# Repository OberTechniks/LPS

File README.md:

# LPS
DIY Lab Power Supply with adjustable voltage and current limiting

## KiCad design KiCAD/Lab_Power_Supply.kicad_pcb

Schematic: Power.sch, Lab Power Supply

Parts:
BAT1, BAT2: 2600mAH; Keystone_Electronics_54; Charge Voltage 4.2V Charge; Manufacturer Part# 54
C1, C9, C12, C13, C15, C16: 0.1uF; C_0805; Manufacturer Part# C0805C104K5RACTU
C2, C3, C4, C17: 47nF; C_0805; Manufacturer Part# C0805C473K5RACTU
C5, C10: 2.2uF; C_0805; Manufacturer Part# UMK212BB7225KG-T
C6: 1nF; C_0805; Manufacturer Part# C0805C102K5RACTU
C7, C8: 0.22uF; C_0805; Manufacturer Part# UMK212B7224KG-T
C11: 1.0uF; C_0805; Manufacturer Part# CL21B105KOFNNNG
C14: 22uF; C_0805; Manufacturer Part# JMK212BJ226MG-T
C18, C19: 100uF; CP_Radial_D8.0mm_P3.50mm; Manufacturer Part# ESY107M050AG3AA
D1: 22V; D_SMA; Manufacturer Part# SMAZ22-13-F
D2: SCR; TO-252-3_TabPin2; Manufacturer Part# MCR12DCMT4G
D3: D_Schottky_ALT; D_SMC; Manufacturer Part# MBRS340T3G
D6: D_Schottky_ALT; D_SMC; Manufacturer Part# MBRS360T3G
F1: 3A; R_1206_HandSoldering; Manufacturer Part# C1Q 3
F2: 6A; R_1206_HandSoldering; Manufacturer Part# C1F 6
J1: BARREL_JACK; PJ-066A; Manufacturer Part# PJ-066A
L1: 10uH; IFSC1515AHER100M01; Manufacturer Part# IFSC1515AHER100M01
L2: 33uH; SRP1265A-330M; Manufacturer Part# SRP1265A-330M
L3: 1uH; 2520_Metric; Manufacturer Part# CIG22E1R0MNE
L4: Ferrite; C_0805; Manufacturer Part# BMB2A0300LN2
Q1: MOSFET N-CH 20V 0.2A EMT3; SC-89; Manufacturer Part# RE1C002UNTCL
Q2: Q_PMOS_GDS; TO-252-3_TabPin2; Manufacturer Part# AOD4189
R1: 1K; R_2512; Manufacturer Part# CRM2512-JW-102ELF
R2: 120; R_0805; Manufacturer Part# RC0805FR-07120RL
R3, R4, R5, R6, R7, R9, R10, R11: 100K; R_0805; Manufacturer Part# RC0805FR-07100KL
R8: 10K; R_0805; Manufacturer Part# RMCF0805JT10K0
R12, R13: 4.7; R_0805; Manufacturer Part# CRCW08054R70FKEA
R14: 0.04; R_2512; Manufacturer Part# CRA2512-FZ-R040ELF
R15: 6.8; R_2512; Manufacturer Part# RPC2512JT6R80
R16: 0.03; R_2512; Manufacturer Part# CRA2512-FZ-R030ELF
TP2, TP3, TP4, TP5, TP6, TP7, TP8, TP9, TP10: TestPoint; SMT_Test_Point; Manufacturer Part# S1751-46R
U4: MAX1873; QSOP-16_3.9x4.9mm_Pitch0.635mm; Manufacturer Part# MAX1873REEE+T
U5: TPS62177; 10-WSON; Manufacturer Part# TPS62177DQCR

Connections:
+3V3: C17.1, L4.2, TP4.1; also elsewhere on the board
/Control/CHARGE_~EN~: R2.2; also elsewhere on the board
/Control/CHG_SENSE_+: L2.2, R16.2, U4.11; also elsewhere on the board
/Control/CHG_SENSE_-: C19.1, F2.1, R16.1, TP3.1, U4.10; also elsewhere on the board
/Control/ICHG_ANALOG: TP10.1, U4.7; also elsewhere on the board
/Output/VSYS: C5.1, C18.1, Q2.3, R13.2, R14.1, TP2.1, U5.2, U5.3; also elsewhere on the board
/Power/VREF: C11.1, R4.1, R10.1, TP9.1, U4.9
/Power/~SLEEP~: U5.8
GND: BAT2.2, C1.2, C2.2, C3.2, C4.2, C5.2, C6.2, C7.1, C9.2, C10.2, C11.2, C12.2, C13.2, C14.2, C15.2, C16.2, C17.2, C18.2, C19.2, D2.1 (K), D6.2, J1.2, J1.3, Q1.2, R1.2, R3.2, R7.2, R11.2, TP5.1, TP6.1, TP7.1, TP8.1, U4.12, U5.1, U5.4, U5.5, U5.6, U5.PAD; also elsewhere on the board
unnamed: BAT1.1, F2.2
unnamed: BAT1.2, BAT2.1
unnamed: C1.1, D1.1, D2.2 (A), D3.2, F1.2
unnamed: C2.1, D1.2, D2.3 (G), R1.1
unnamed: C3.1, U4.5
unnamed: C4.1, U4.3
unnamed: C6.1, R8.1, U4.4
unnamed: C7.2, C8.2, D3.1, R12.2, R14.2, U4.15
unnamed: C8.1, U4.13
unnamed: C9.1, R8.2
unnamed: C10.1, U4.16
unnamed: C12.1, R12.1, U4.2
unnamed: C13.1, R13.1, U4.1
unnamed: C14.1, C15.1, L1.2, L3.1, R9.1, R15.1, U5.10
unnamed: C16.1, L3.2, L4.1, R15.2
unnamed: D6.1, L2.1, Q2.2
unnamed: F1.1, J1.1
unnamed: L1.1, U5.9
unnamed: Q1.1, R2.1, R3.1
unnamed: Q1.3, R6.2, R7.1, U4.6
unnamed: Q2.1, U4.14
unnamed: R4.2, R5.1
unnamed: R5.2, R6.1
unnamed: R9.2, U5.7
unnamed: R10.2, R11.1, U4.8

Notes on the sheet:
Ichg = 0.2V(Vichg / Vref)/Rcsb Vichg / Vref = 1/4 Rcsb = 0.030 Ohms Ichg = 1.67A
Vichg = (1/4) Vref = 1.05V Drop below 500mV to disable charging
Input Current Limit Iin = 0.1V/RCSS 0.1V/0.04 = 2.5A
DC INPUT, 12V-20V, 2.5A
BATTERY CHARGING & SYSTEM VOLTAGE
DIGITAL POWER RAIL
Max Output 3.3V, 500mA
TEST POINTS

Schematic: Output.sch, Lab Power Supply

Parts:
C20: 6800pF; C_0805; Manufacturer Part# C0805C682K5RACTU
C21, C34: 47pF; C_0805; Manufacturer Part# 500R15N470JV4T
C22: 4.7uF; C_0805; Manufacturer Part# CL21A475KLCLQNC
C23, C24, C25, C27, C35: 22uF; CP_Elec_6.3x5.3; Manufacturer Part# EEE-1HA220WP
C26, C28, C29, C30, C31, C62: 0.1uF; C_0805; Manufacturer Part# C0805C104K5RACTU
C32: 1nF; C_0805; Manufacturer Part# C0805C102K5RACTU
C33: 22pF; C_0805; Manufacturer Part# C0805C220J5GACTU
D7: D_Schottky_AAK; V20PW10-M3; Manufacturer Part# V20PW10-M3/I
D8, D9, D11: D_Schottky_ALT; D_SMC; Manufacturer Part# MBRS360T3G
D10: 10V; D_MiniMELF; Manufacturer Part# TZM5240B-GS08
D12: 24V; D_SMA; Manufacturer Part# 3SMAJ5934B-TP
F3: 2A; R_1206; Manufacturer Part# C1Q 2
J2: OUTPUT; SolderWirePad_2x_2mmDrill; Manufacturer Part# 43650-0228
L5: 1uH; SRP1245A-1R0M; Manufacturer Part# SRP1245A-1R0M
Q3: Q_NMOS_GDS; TO-252-2; Manufacturer Part# IRLR6225TRPBF
Q4: Q_PNP_BEC; SOT-23; Manufacturer Part# MMBT4403
Q5: Q_PMOS_GDS; TO-220-3_Vertical; Manufacturer Part# IRF9640PBF
Q6: Q_NMOS_GDS; TO-263-2; Manufacturer Part# IRF530NSTRLPBF
R17, R18, R19, R29, R31, R32, R38: 10K; R_0805; Manufacturer Part# RMCF0805JT10K0
R20: 80.6K; R_0805; Manufacturer Part# RC0805FR-0780K6L
R21, R36: 4.7K; R_0805; Manufacturer Part# RC0805JR-074K7L
R22, R23: 100K; R_0805; Manufacturer Part# RC0805FR-07100KL
R24, R25: 1M; R_0805; Manufacturer Part# RC0805JR-071ML
R26: 1K; R_0805; Manufacturer Part# CRM2512-JW-102ELF
R27: 3K; R_0805; Manufacturer Part# RC0805FR-073KL
R28: 27K; R_0805; Manufacturer Part# RC0805FR-0727KL
R30, R37, R40: 1K; R_2512; Manufacturer Part# CRM2512-JW-102ELF
R33: 47K; R_0805; Manufacturer Part# RC0805JR-0747KL
R34: 120; R_0805; Manufacturer Part# RC0805FR-07120RL
R35: 470; R_0805; Manufacturer Part# RC0805JR-07470RL
R39: .1; R_1206; Manufacturer Part# PT1206FR-070R1L
SW5: SW_SPST; R1966ABLKBLKGR; Manufacturer Part# R1966ABLKBLKGR
TP11, TP12, TP13, TP14, TP15, TP16, TP17: TestPoint; SMT_Test_Point; Manufacturer Part# S1751-46R
U2, U3: LM324; SOIC-14_3.9x8.7mm_Pitch1.27mm; Manufacturer Part# LM324ADR
U6: LTC1871-1; MSOP-10_3x3mm_Pitch0.5mm; Manufacturer Part# LTC1871EMS-1#PBF
U7: MCP40D17T-104E/LT; SOT-363_SC-70-6; Manufacturer Part# MCP40D17T-104E/LT

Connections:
+3V3: C24.1, C25.1, C26.1, C27.1, C28.1, C29.1, D7.3, D10.1, Q5.3, R37.2, TP11.1, U2.4 (V+), U3.4 (V+), U7.1 (VDD), U7.6 (W); also elsewhere on the board
/Control/BOOST_EN: R17.2, TP16.1, U6.1; also elsewhere on the board
/Control/CURRENT_SET: R30.2; also elsewhere on the board
/Control/I2C_SCL: U7.4 (SDA); also elsewhere on the board
/Control/I2C_SDA: U7.3 (SCL); also elsewhere on the board
/Control/ISENSE_+: D11.1, R22.1, R38.2, R39.2; also elsewhere on the board
/Control/ISENSE_-: C35.1, D12.1, F3.2, Q6.2, R23.1, R32.1, R39.1; also elsewhere on the board
/Control/VOLTAGE_SET: U2.3 (+); also elsewhere on the board
/Output/GATE: Q3.1, TP13.1, U6.7
/Output/INTVCC: C22.1, TP14.1, U6.5, U6.8
/Output/ITH: C21.2, R18.2, TP15.1, U6.2
/Output/OUTPUT: J2.1, SW5.2, TP12.1
/Output/VSYS: C23.1, C62.1, L5.1, U6.9; also elsewhere on the board
GND: C20.1, C21.1, C22.2, C23.2, C24.2, C25.2, C26.2, C27.2, C28.2, C29.2, C30.2, C35.2, C62.2, D8.1, J2.2, Q3.3, Q4.3, Q6.3, R17.1, R20.1, R21.1, R24.2, R26.2, R27.2, R29.1, R38.1, R40.1, TP17.1, U2.11 (V-), U3.11 (V-), U6.6, U7.2 (VSS); also elsewhere on the board
unnamed: C20.2, R19.1
unnamed: C30.1, R28.2, R29.2, R31.2, U2.1
unnamed: C31.1, C32.2, R35.2, U3.7
unnamed: C31.2, R30.1, U3.6 (-)
unnamed: C32.1, D9.2, R35.1
unnamed: C33.1, C34.1, R36.2, U2.7
unnamed: C33.2, R33.2
unnamed: C34.2, R34.2
unnamed: D7.1, D7.2, L5.2, Q3.2, U6.10
unnamed: D8.2, R32.2, U2.5 (+)
unnamed: D9.1, D10.2, Q4.1, R36.1
unnamed: D11.2, Q5.2
unnamed: D12.2, Q6.1, R40.2
unnamed: F3.1, SW5.1
unnamed: Q4.2, Q5.1, R37.1
unnamed: R18.1, R19.2
unnamed: R20.2, U6.4
unnamed: R21.2, U6.3, U7.5 (B)
unnamed: R22.2, R24.1, U3.3 (+)
unnamed: R23.2, R25.1, U3.2 (-)
unnamed: R25.2, R26.1, U3.1, U3.5 (+)
unnamed: R27.1, R28.1, U2.2 (-)
unnamed: R31.1, R33.1, R34.1, U2.6 (-)

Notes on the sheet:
BOOST CONVERTER PRE-REGULATION
TEST POINTS
CONSTANT VOLTAGE LOOP
CONSTANT CURRENT LOOP
VCC = 1.230V*(1+R1/R2)
100K DIGITAL POT

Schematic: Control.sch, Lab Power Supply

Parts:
C36, C37, C38, C39, C40, C41, C42, C43, C44, C45, C46, C47, C49, C50, C51, C54, C55, C57, C58, C61: 0.1uF; C_0805; Manufacturer Part# C0805C104K5RACTU
C48: 22uF; R_0805; Manufacturer Part# JMK212BJ226MG-T
C52, C53: 12pF; C_0805; Manufacturer Part# CL21C120JBANNNC
C56, C59: 22uF; C_0805; Manufacturer Part# JMK212BJ226MG-T
C60: 1.0uF; C_0805; Manufacturer Part# CL21B105KOFNNNG
D13: 568-0102-173F; Manufacturer Part# 5680102173F
D14: B; APG0603PBC-TT-5MAV; Manufacturer Part# APG0603PBC-TT-5MAV
J3: ICSP_Header; Socket_Strip_Straight_1x06_Pitch2.54mm
J4: Debug Connector; Socket_Strip_Straight_1x06_Pitch2.54mm; Manufacturer Part# M20-9990646
JP1, JP2, JP3, JP4: Jumper_3_Pos; Socket_Strip_Straight_1x03_Pitch2.54mm; Manufacturer Part# 61300311121
Q7, Q8, Q9, Q10, Q11: MOSFET N-CH 20V 0.2A EMT3; SC-89; Manufacturer Part# RE1C002UNTCL
Q12: Q_PMOS_GSD; SOT-23; Manufacturer Part# FDN302P
Q13: Q_PNP_BEC; MMBT3906TT1G; Manufacturer Part# MMBT3906TT1G
R41, R43, R45, R46, R48, R49, R55, R56, R86, R90, R98: 120; R_0805; Manufacturer Part# RC0805FR-07120RL
R42, R44, R47, R50, R59, R60, R61, R88: 100K; R_0805; Manufacturer Part# RC0805FR-07100KL
R51, R52, R53, R54, R57, R58, R62, R63, R64, R65, R66, R67, R68, R69, R70, R74, R78, R79, R80, R81, R87, R89, R97: 10K; R_0805; Manufacturer Part# RMCF0805JT10K0
R71, R72, R76, R77: 10; R_0805; Manufacturer Part# RC0805JR-0710RL
R73, R82, R83, R99: 0; R_0805; Manufacturer Part# RMCF0805ZT0R00
R75: 470; R_0805; Manufacturer Part# RC0805JR-07470RL
R84, R85, R91, R92, R93, R94, R95, R96: 4.7K; R_0805; Manufacturer Part# RC0805JR-074K7L
RV1: 10K; 3361P-1-103GLF; Manufacturer Part# 3361P-1-103GLF
SW1, SW2: EN11-VSM1AF20; Manufacturer Part# EN11-VSM1AF20
SW3: SW_Push; TL1105SF160Q; Manufacturer Part# TL1105SF160Q
SW6: Reset; 7914J-1-000E; Manufacturer Part# 7914J-1-000E
TP18, TP19, TP20, TP21, TP22, TP23, TP24, TP25, TP26, TP27: TestPoint; SMT_Test_Point; Manufacturer Part# S1751-46R
U1: 74HC14; TSSOP-14_4.4x5mm_Pitch0.65mm; Manufacturer Part# SN74HC14PWR
U8: INA226AIDGSR; MSOP-10_3x3mm_Pitch0.5mm; Manufacturer Part# INA226AIDGSR
U9: PIC32MX350F256L-I/PT; TQFP-100_12x12mm_Pitch0.4mm; Manufacturer Part# PIC32MX350F256L-I/PT
U10: 23LC512; SOIC-8_3.9x4.9mm_Pitch1.27mm; Manufacturer Part# 23LC512-I/SN
U11: MCP4822; SOIC-8_3.9x4.9mm_Pitch1.27mm; Manufacturer Part# MCP4822-E/SN
U12: LTC2943; DFN-8-1EP_3x3mm_Pitch0.5mm; Manufacturer Part# LTC2943IDD#PBF
U13: RN4678; Manufacturer Part# RN4678
X1: LCD-09052; Socket_Strip_Straight_2x08_Pitch2.54mm; Manufacturer Part# LCD-09052
Y1: Crystal_Small; ABS25-32.768KHZ-T; Manufacturer Part# ABS25-32.768KHZ-T

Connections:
+3V3: C43.1, C44.1, C45.1, C46.1, C47.1, C49.1, C50.1, C51.1, C55.1, C57.1, C58.2, J3.2, Q12.3, Q13.2, R46.1, R49.1, R55.1, R56.1, R57.2, R58.2, R62.2, R63.2, R64.1, R65.1, R66.1, R70.2, R73.1, R74.2, R78.2, R79.2, R80.2, R81.2, R82.2, R83.2, R84.2, R85.2, R87.2, R89.2, R94.2, R95.2, R96.2, R97.2, R99.1, U1.14 (VCC), U9.2 (VDD), U9.16 (VDD), U9.30 (AVDD), U9.37 (VDD), U9.46 (VDD), U9.62 (VDD), U9.86 (VDD); also elsewhere on the board
/Control/BOOST_EN: U9.93 (PMD0/RE0); also elsewhere on the board
/Control/BT_CTS: U9.77 (AN25/RPD2/RD2), U13.17
/Control/BT_P04: U9.81 (RPD4/PMWR/RD4), U13.11
/Control/BT_P05: U9.82 (RPD5/PMRD/RD5), U13.16
/Control/BT_P15: U9.83 (PMD14/RD6), U13.12
/Control/BT_P31: U9.84 (PMD15/RD7), U13.24
/Control/BT_P32: U9.68 (RPD8/RTCC/RD8), U13.25
/Control/BT_P33: U9.69 (RPD9/RD9), U13.26
/Control/BT_P34: U9.70 (RPD10/PMCS2/RD10), U13.27
/Control/BT_P36: U9.71 (RPD11/PMCS1/RD11), U13.28
/Control/BT_P37: U9.79 (RPD12/PMD12/RD12), U13.29
/Control/BT_RTS: U9.78 (AN26/RPD3/RD3), U13.15
/Control/BT_RXD: U9.76 (AN24/RPD1/RD1), U13.23
/Control/BT_SW_BTN: U9.80 (PMD13/RD13), U13.5
/Control/BT_TXD: U9.72 (RPD0/RD0), U13.22
/Control/BT_WAKEUP: U9.47 (RPD14/RD14), U13.9
/Control/BT_~RST~: R97.1, U9.48 (RPD15/RD15), U13.21
/Control/CHARGE_~EN~: U9.20 (AN5/C1INA/RPB5/RB5); also elsewhere on the board
/Control/CHG_SENSE_+: U12.1; also elsewhere on the board
/Control/CHG_SENSE_-: R59.2, U12.8; also elsewhere on the board
/Control/CURRENT_MONITOR_ALERT: R70.1, U8.3, U9.88 (RPF1/PMD10/RF1)
/Control/CURRENT_SET: TP19.1, U11.6 (VoutB); also elsewhere on the board
/Control/DEBUG_RXD: J4.4, U9.40 (RPF12/RF12)
/Control/DEBUG_TXD: J4.5, U9.39 (RPF13/RF13)
/Control/ENC1_A: C39.1, R54.2, TP24.1, U9.26 (PGEC2/AN6/RPB6/RB6)
/Control/ENC1_B: C37.1, R53.2, TP25.1, U9.27 (PGED2/AN7/RPB7/CTED3/RB7)
/Control/ENC1_SW: U1.2, U9.34 (CVREFOUT/AN10/RPB10/RB10)
/Control/ENC2_A: C38.1, R52.2, TP26.1, U9.32 (AN8/RPB8/CTED10/RB8)
/Control/ENC2_B: C36.1, R51.2, TP27.1, U9.33 (AN9/RPB9/CTED4/RB9)
/Control/ENC2_SW: U1.4, U9.35 (AN11/PMA12/RB11)
/Control/I2C_SCL: R84.1, R85.1, TP23.1, U8.5, U9.57 (SCL1/RG2), U12.4; also elsewhere on the board
/Control/I2C_SDA: TP22.1, U8.4, U9.56 (SDA1/RG3), U12.5; also elsewhere on the board
/Control/ICHG_ANALOG: U9.22 (PGED3/AN3/C2INA/RPB3/RB3); also elsewhere on the board
/Control/ISENSE_+: R76.2; also elsewhere on the board
/Control/ISENSE_-: R77.2, U8.8; also elsewhere on the board
/Control/LCD_BL_CTRL: R98.1, U9.67 (RPA15/RA15)
/Control/LCD_DB0: U9.17 (TMS/CTED1/RA0), X1.7
/Control/LCD_DB1: U9.38 (TCK/CTED2/RA1), X1.8
/Control/LCD_DB2: U9.58 (SCL2/RA2), X1.9
/Control/LCD_DB3: U9.59 (SDA2/RA3), X1.10
/Control/LCD_DB4: U9.60 (TDI/CTED9/RA4), X1.11
/Control/LCD_DB5: U9.61 (TDO/RA5), X1.12
/Control/LCD_DB6: U9.91 (TRCLK/RA6), X1.13
/Control/LCD_DB7: U9.92 (TRD3/CTED8/RA7), X1.14
/Control/LCD_OP_EN: U9.28 (VREF-/CVREF-/PMA7/RA9), X1.6
/Control/LCD_PWR_EN: R86.1, U9.23 (PGEC3/AN2/C2INB/CTED12/RB2)
/Control/LCD_R/W: U9.29 (VREF+/CVREF+/PMA6/RA10), X1.5
/Control/LCD_RS: U9.66 (RPA14/RA14), X1.4
/Control/LED_GREEN: R41.1
/Control/LED_ORANGE: R45.1
/Control/LED_RED: R43.1
/Control/LED_YELLOW: R48.1
/Control/PGC: R72.2, U9.24 (PGEC1/AN1/RPB1/CTED12/RB1)
/Control/PGD: R71.2, U9.25 (PGED1/AN0/RPB0/RB0)
/Control/REMOTE_SW: U1.6, U9.41 (AN12/PMA11/RB12)
/Control/SPI_CLK: TP21.1, U9.55 (RPF6/SCK1/INT0/RF6), U10.6, U11.2 (~CS~)
/Control/SPI_SDI: U9.54 (RPF7/RF7), U10.2
/Control/VBAT_MONITOR: R60.1, R61.2, U9.21 (AN4/C1INB/RB4)
/Control/VOLTAGE_SET: TP18.1, U11.8 (VoutA); also elsewhere on the board
/Control/~LDAC~: R78.1, U9.50 (RPF5/PMA8/RF5), U11.3 (SCK)
/Control/~SRAM_CS~: R81.1, U9.52 (RPF2/RF2), U10.1
/Control/~SRAM_HOLD~: R79.1, U9.51 (RPF3/RF3), U10.7
GND: C36.2, C37.2, C38.2, C39.2, C40.2, C41.2, C42.2, C43.2, C44.2, C45.2, C46.2, C47.2, C48.1, C49.2, C50.2, C51.2, C52.1, C53.1, C55.2, C56.1, C57.2, C58.1, C59.1, C60.1, C61.2, J3.3, J4.1, Q7.2, Q8.2, Q9.2, Q10.2, Q11.2, R42.1, R44.1, R47.1, R50.1, R61.1, R88.1, R91.1, R92.1, R93.1, RV1.3, SW1.2 (C), SW1.4, SW2.2 (C), SW2.4, SW3.2, SW6.1, U1.7 (GND), U8.1, U8.2, U8.7, U9.15 (VSS), U9.31 (AVSS), U9.36 (VSS), U9.45 (VSS), U9.65 (VSS), U9.75 (VSS), U10.4, U11.7 (VSS), U12.2, U12.3, U12.7, U12.9, U13.1, U13.2, U13.31, U13.32, U13.33, X1.1, X1.16; also elsewhere on the board
unnamed: C40.1, R67.1, U1.5
unnamed: C41.1, R68.1, U1.3
unnamed: C42.1, R69.1, U1.1
unnamed: C48.2, JP1.2
unnamed: C52.2, U9.73 (SOSCI/RPC13/RC13), Y1.1
unnamed: C53.2, U9.74 (SOSCO/RPC14/T1CK/RC14), Y1.2
unnamed: C54.1, R76.1, U8.10
unnamed: C54.2, R77.1, U8.9
unnamed: C56.2, U9.85 (VCAP)
unnamed: C59.2, R99.2, U13.4
unnamed: C60.2, R90.1, U13.6, U13.7
unnamed: C61.1, Q12.2, RV1.1, X1.2
unnamed: D13.1, Q7.3
unnamed: D13.2, R46.2
unnamed: D13.3, Q8.3
unnamed: D13.4, R49.2
unnamed: D13.5, Q9.3
unnamed: D13.6, R55.2
unnamed: D13.7, Q10.3
unnamed: D13.8, R56.2
unnamed: D14.1, U13.30
unnamed: D14.2, R90.2
unnamed: J3.1, JP1.3, R74.1, R75.1, SW6.2
unnamed: J3.4, R71.1
unnamed: J3.5, R72.1
unnamed: JP2.1, R91.2
unnamed: JP2.2, R94.1
unnamed: JP2.3, U13.18
unnamed: JP3.1, R92.2
unnamed: JP3.2, R95.1
unnamed: JP3.3, U13.19
unnamed: JP4.1, R93.2
unnamed: JP4.2, R96.1
unnamed: JP4.3, U13.20
unnamed: Q7.1, R41.2, R42.2
unnamed: Q8.1, R43.2, R44.2
unnamed: Q9.1, R45.2, R47.2
unnamed: Q10.1, R48.2, R50.2
unnamed: Q11.1, R86.2, R88.2
unnamed: Q11.3, Q12.1, R89.1
unnamed: Q13.1, R98.2
unnamed: Q13.3, X1.15
unnamed: R51.1, R62.1, SW2.3 (B)
unnamed: R52.1, R57.1, SW2.1 (A)
unnamed: R53.1, R63.1, SW1.3 (B)
unnamed: R54.1, R58.1, SW1.1 (A)
unnamed: R59.1, R60.2
unnamed: R64.2, R67.2, SW3.1
unnamed: R65.2, R68.2, SW2.5
unnamed: R66.2, R69.2, SW1.5
unnamed: R73.2, U8.6
unnamed: R75.2, U9.13 (~MCLR~)
unnamed: R82.1, U10.8
unnamed: R83.1, U11.1 (VDD)
unnamed: R87.1, U12.6
unnamed: RV1.2, X1.3

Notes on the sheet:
12-bit DAC 0-2.048V Output
LED INDICATORS
TEST POINTS
DIGITAL POWER RAIL
16 bit ADC 50 mOhm Shunt 0-1A => 0-50mVolts 2.5uVolt Step Size 50uAmps resolution
OUTPUT SETPOINTS
OUTPUT MONITORING
BATTERY CHARGE GAUGE
LCD DISPLAY
FILTERED QUADRATURE ENCODERS PB SWITCHES W/ DEBOUNCING
VBAT Nominal = 8.4V 8.4V/3 = 2.8V
uC Decoupling Caps
Use jumper to disconnect cap from MCLR when programming uC
DATA LOGGING SRAM
512Kbit (64Kx8)
BLUETOOTH MODULE
Supports BLE & Classic
DEBUG
BATTERY MONITOR

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
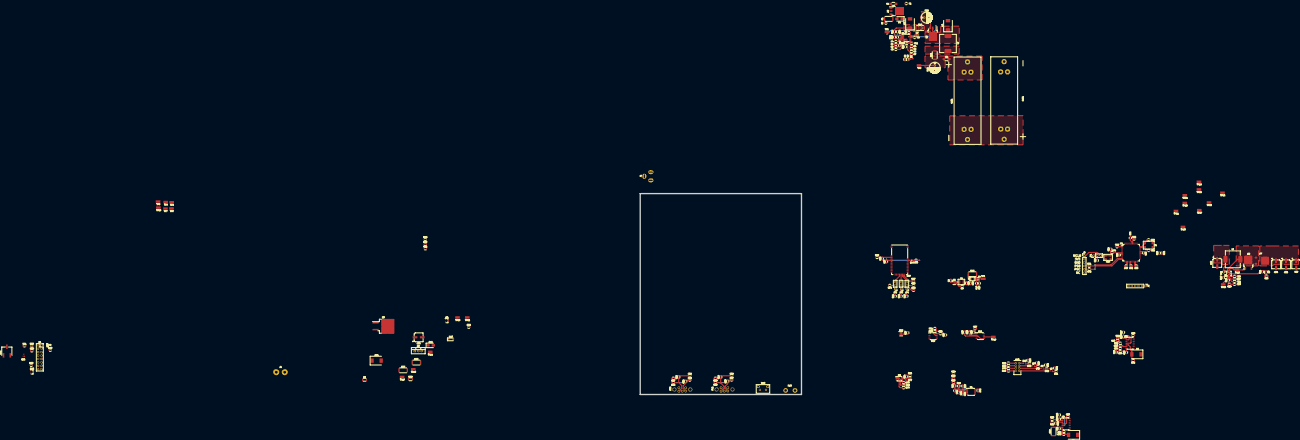
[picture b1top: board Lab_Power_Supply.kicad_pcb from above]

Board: 2 copper layers, 251 parts (0 on the bottom side), 172 nets.

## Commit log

2019-01-16 Initial project files commit to repo
